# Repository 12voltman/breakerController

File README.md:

# breakerController
Chainable system for internet control of remotely switchable breakers

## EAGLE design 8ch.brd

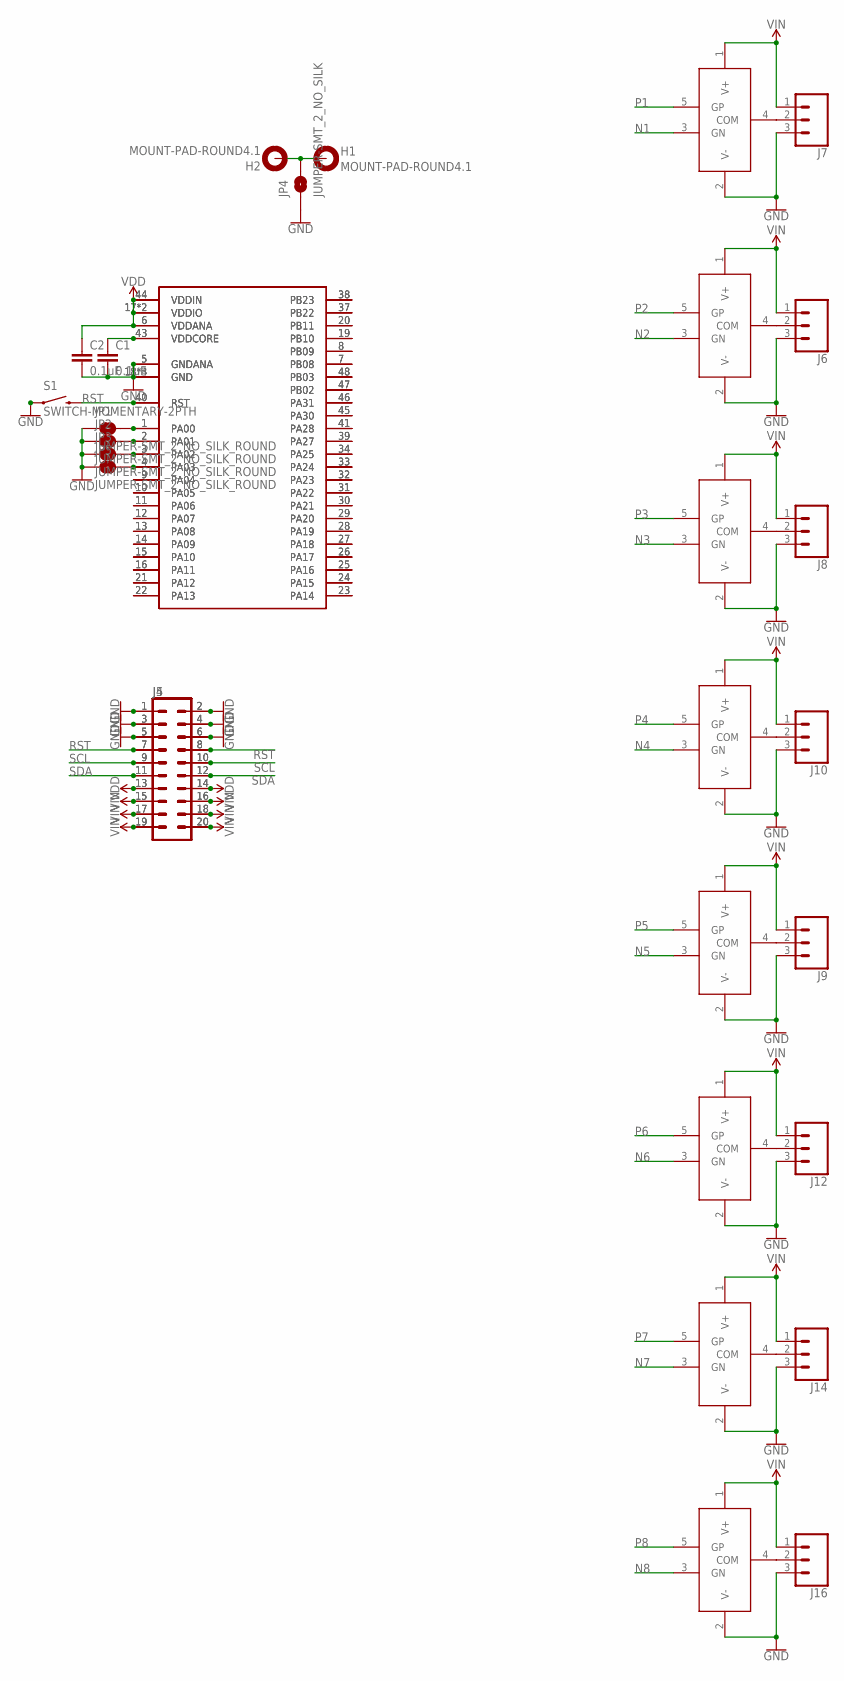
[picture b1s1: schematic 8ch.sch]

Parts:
C1, C2: 0.1uF; 0603
H1, H2: MOUNT-PAD-ROUND4.1; 4,1-PAD
J4, J5: CONN_10X2; 2X10
J6, J7, J8, J9, J10, J12, J14, J16: CONN_03-SCREW-5MM; SCREWTERMINAL-5MM-3
JP1, JP2, JP3, JP5: JUMPER-SMT_2_NO_SILK_ROUND; SMT-JUMPER_2_NO_SILK_ROUND
JP4: JUMPER-SMT_2_NO_SILK; SMT-JUMPER_2_NO_SILK
S1: SWITCH-MOMENTARY-2PTH; TACTILE-PTH
U$1: ATSAMD2G1A-M; QFN48_7X7
U$2, U$3, U$4, U$5, U$6, U$8, U$10, U$12: COMPBJT; SOT23-5
U$7: ATSAMD2G1A-A; TQFP48_7X7

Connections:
GND: C1.2, C2.2, J4.1, J4.2, J4.3, J4.4, J4.5, J4.6, J5.1, J5.2, J5.3, J5.4, J5.5, J5.6, J6.3, J7.3, J8.3, J9.3, J10.3, J12.3, J14.3, J16.3, JP1.1, JP2.1, JP3.1, JP4.1, JP5.1, S1.1, S1.2 (1), U$1.5 (GNDANA), U$1.18 (GND), U$1.35 (GND), U$1.42 (GND), U$1.EXP (GND), U$2.2 (V-), U$3.2 (V-), U$4.2 (V-), U$5.2 (V-), U$6.2 (V-), U$7.5 (GNDANA), U$7.18 (GND), U$7.35 (GND), U$7.42 (GND), U$8.2 (V-), U$10.2 (V-), U$12.2 (V-)
N1: U$3.3 (GN)
N2: U$2.3 (GN)
N3: U$4.3 (GN)
N4: U$6.3 (GN)
N5: U$5.3 (GN)
N6: U$8.3 (GN)
N7: U$10.3 (GN)
N8: U$12.3 (GN)
unnamed: H1.B4,1, H2.B4,1, JP4.2
unnamed: J6.2, U$2.4 (COM)
unnamed: J7.2, U$3.4 (COM)
unnamed: J8.2, U$4.4 (COM)
unnamed: J9.2, U$5.4 (COM)
unnamed: J10.2, U$6.4 (COM)
unnamed: C1.1, U$1.43 (VDDCORE), U$7.43 (VDDCORE)
unnamed: J12.2, U$8.4 (COM)
unnamed: J14.2, U$10.4 (COM)
unnamed: J16.2, U$12.4 (COM)
unnamed: JP1.2, U$1.1 (PA00), U$7.1 (PA00)
unnamed: JP2.2, U$1.2 (PA01), U$7.2 (PA01)
unnamed: JP3.2, U$1.3 (PA02), U$7.3 (PA02)
unnamed: JP5.2, U$1.4 (PA03), U$7.4 (PA03)
unnamed: U$1.9 (PA04), U$7.9 (PA04)
unnamed: U$1.10 (PA05), U$7.10 (PA05)
unnamed: U$1.11 (PA06), U$7.11 (PA06)
unnamed: U$1.12 (PA07), U$7.12 (PA07)
unnamed: U$1.13 (PA08), U$7.13 (PA08)
unnamed: U$1.14 (PA09), U$7.14 (PA09)
unnamed: U$1.15 (PA10), U$7.15 (PA10)
unnamed: U$1.16 (PA11), U$7.16 (PA11)
unnamed: U$1.21 (PA12), U$7.21 (PA12)
unnamed: U$1.22 (PA13), U$7.22 (PA13)
unnamed: U$1.23 (PA14), U$7.23 (PA14)
unnamed: U$1.24 (PA15), U$7.24 (PA15)
unnamed: U$1.25 (PA16), U$7.25 (PA16)
unnamed: U$1.26 (PA17), U$7.26 (PA17)
unnamed: U$1.27 (PA18), U$7.27 (PA18)
unnamed: U$1.28 (PA19), U$7.28 (PA19)
unnamed: U$1.29 (PA20), U$7.29 (PA20)
unnamed: U$1.30 (PA21), U$7.30 (PA21)
unnamed: U$1.31 (PA22), U$7.31 (PA22)
unnamed: U$1.32 (PA23), U$7.32 (PA23)
unnamed: U$1.33 (PA24), U$7.33 (PA24)
unnamed: U$1.34 (PA25), U$7.34 (PA25)
unnamed: U$1.41 (PA28), U$7.41 (PA28)
unnamed: U$1.45 (PA30), U$7.45 (PA30)
unnamed: U$1.46 (PA31), U$7.46 (PA31)
unnamed: U$1.47 (PB02), U$7.47 (PB02)
unnamed: U$1.48 (PB03), U$7.48 (PB03)
unnamed: U$1.7 (PB08), U$7.7 (PB08)
unnamed: U$1.8 (PB09), U$7.8 (PB09)
unnamed: U$1.19 (PB10), U$7.19 (PB10)
unnamed: U$1.20 (PB11), U$7.20 (PB11)
unnamed: U$1.37 (PB22), U$7.37 (PB22)
unnamed: U$1.38 (PB23), U$7.38 (PB23)
unnamed: U$1.39 (PA27), U$7.39 (PA27)
P1: U$3.5 (GP)
P2: U$2.5 (GP)
P3: U$4.5 (GP)
P4: U$6.5 (GP)
P5: U$5.5 (GP)
P6: U$8.5 (GP)
P7: U$10.5 (GP)
P8: U$12.5 (GP)
RST: J4.7, J4.8, J5.7, J5.8, S1.3 (2), S1.4 (2), U$1.40 (RST), U$7.40 (RST)
SCL: J4.9, J4.10, J5.9, J5.10
SDA: J4.11, J4.12, J5.11, J5.12
VDD: C2.1, J4.13, J4.14, J5.13, J5.14, U$1.6 (VDDANA), U$1.17 (VDDIO), U$1.36 (VDDIO), U$1.44 (VDDIN), U$7.6 (VDDANA), U$7.17 (VDDIO), U$7.36 (VDDIO), U$7.44 (VDDIN)
VIN: J4.15, J4.16, J4.17, J4.18, J4.19, J4.20, J5.15, J5.16, J5.17, J5.18, J5.19, J5.20, J6.1, J7.1, J8.1, J9.1, J10.1, J12.1, J14.1, J16.1, U$2.1 (V+), U$3.1 (V+), U$4.1 (V+), U$5.1 (V+), U$6.1 (V+), U$8.1 (V+), U$10.1 (V+), U$12.1 (V+)

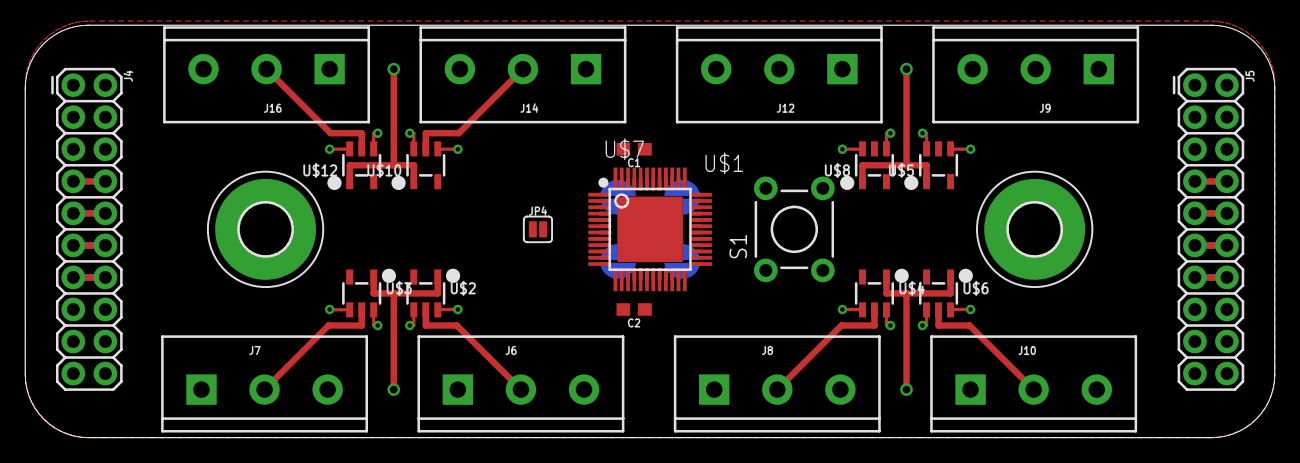
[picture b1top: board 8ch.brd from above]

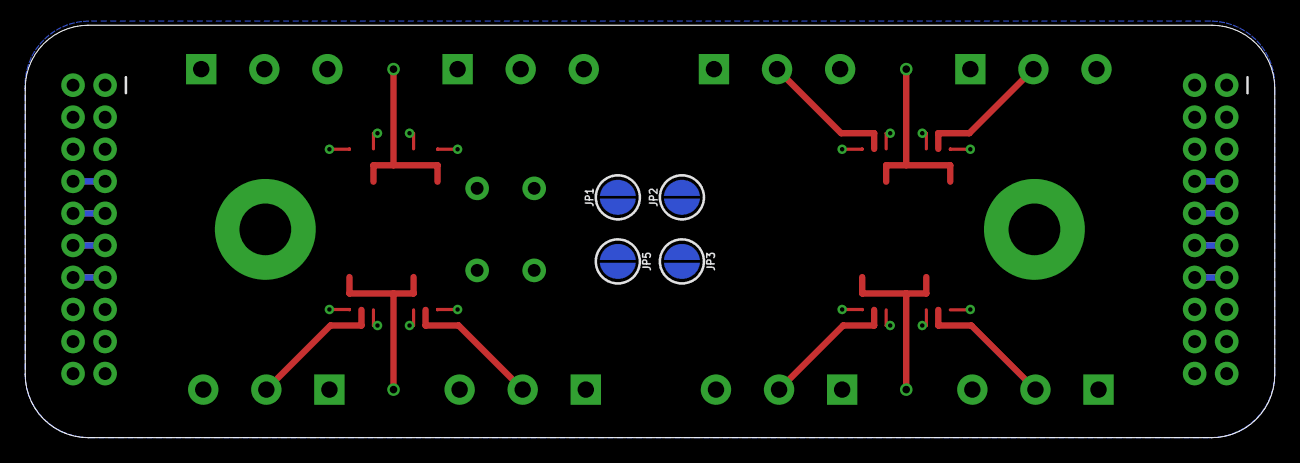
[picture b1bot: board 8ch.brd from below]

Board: 2 copper layers, 99.0 x 32.7 mm, 30 parts (4 on the bottom side), 54 nets.

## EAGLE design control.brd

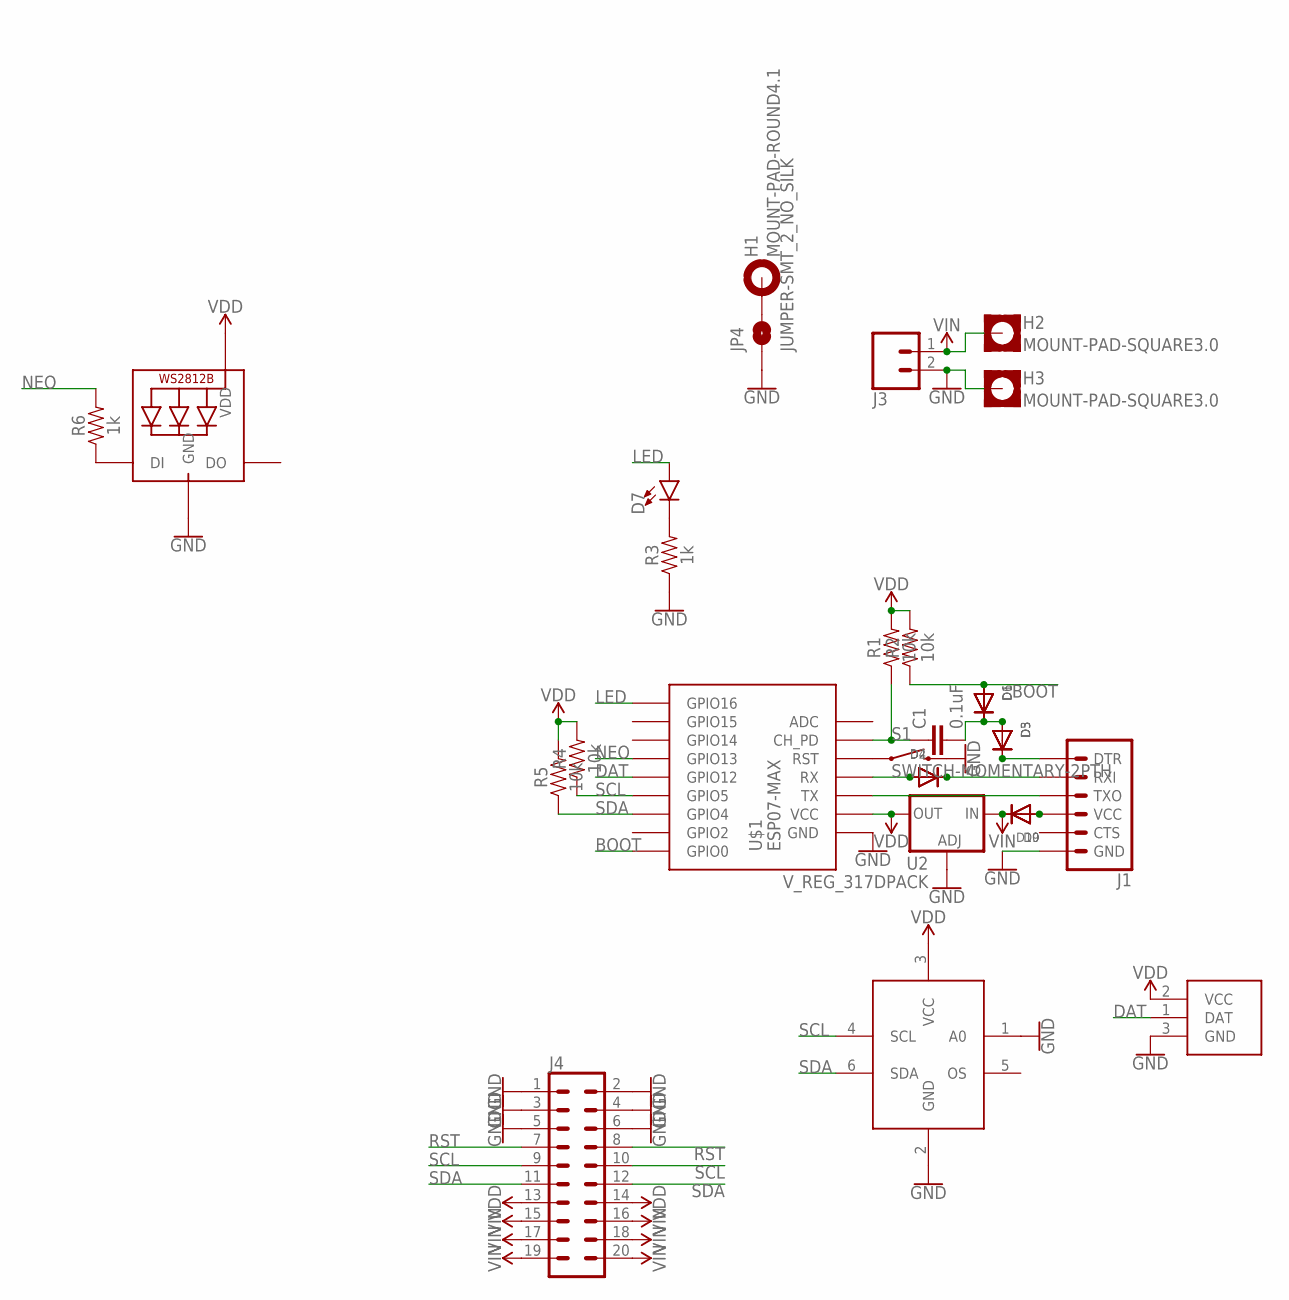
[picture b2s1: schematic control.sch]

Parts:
C1: 0.1uF; 0603
D1, D2, D3, D9: DIODESOD-123; SOD-123
D4, D5, D6, D10: DIODE_SOD-123FL; SOD-123FL
D7: LED0603; LED-0603
H1: MOUNT-PAD-ROUND4.1; 4,1-PAD
H2, H3: MOUNT-PAD-SQUARE3.0; 3,0-PAD-SQUARE
J1: 6_PIN_SERIAL_TARGETSILK; 6_PIN_SERIAL_TARGET_SIDE_W_SILK
J3: CONN_025MM; SCREWTERMINAL-5MM-2
J4: CONN_10X2; 2X10
JP4: JUMPER-SMT_2_NO_SILK; SMT-JUMPER_2_NO_SILK
LED1: WS2812BCOMBO; COMBONEO
R1, R2, R4, R5: 10k; 0603
R3, R6: 1k; 0603
S1: SWITCH-MOMENTARY-2PTH; TACTILE-PTH
U2: V_REG_317DPACK; V-REG_DPACK
U$1: ESP07-MAX
U$2: PCT2075GV; SOT23-6
U$3: ATSHA204A; SOT23

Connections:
BOOT: D1.A, D6.A, R2.1, U$1.P11 (GPIO0)
DAT: U$1.P05 (GPIO12), U$3.1 (DAT)
GND: H3.B3,0, J1.P$6 (GND), J3.2, J4.1, J4.2, J4.3, J4.4, J4.5, J4.6, JP4.1, LED1.VSS1 (GND), LED1.VSS2 (GND), R3.1, S1.3 (2), S1.4 (2), U2.1 (ADJ), U$1.P08 (GND), U$2.1 (A0), U$2.2 (GND), U$3.3 (GND)
LED: D7.A, U$1.P03 (GPIO16)
unnamed: H1.B4,1, JP4.2
unnamed: C1.1, R1.1, U$1.P02 (CH_PD)
unnamed: D2.A, D4.A, U$1.P14 (RX)
unnamed: J1.P$2 (TXO), U$1.P15 (TX)
unnamed: S1.1, S1.2 (1), U$1.P00 (RST)
unnamed: LED1.DIN1 (DI), LED1.DIN2 (DI), R6.1
unnamed: D2.C, D4.C, J1.P$3 (RXI)
unnamed: D3.C, D5.C, J1.P$1 (DTR)
unnamed: D7.C, R3.2
unnamed: D9.A, D10.A, J1.P$4 (VCC)
unnamed: C1.2, D1.C, D3.A, D5.A, D6.C
NEO: R6.2, U$1.P06 (GPIO13)
RST: J4.7, J4.8
SCL: J4.9, J4.10, R4.1, U$1.P12 (GPIO5), U$2.4 (SCL)
SDA: J4.11, J4.12, R5.1, U$1.P13 (GPIO4), U$2.6 (SDA)
VDD: J4.13, J4.14, LED1.VDD1 (VDD), LED1.VDD2 (VDD), R1.2, R2.2, R4.2, R5.2, U2.4 (OUT), U$1.P07 (VCC), U$2.3 (VCC), U$3.2 (VCC)
VIN: D9.C, D10.C, H2.B3,0, J3.1, J4.15, J4.16, J4.17, J4.18, J4.19, J4.20, U2.3 (IN)

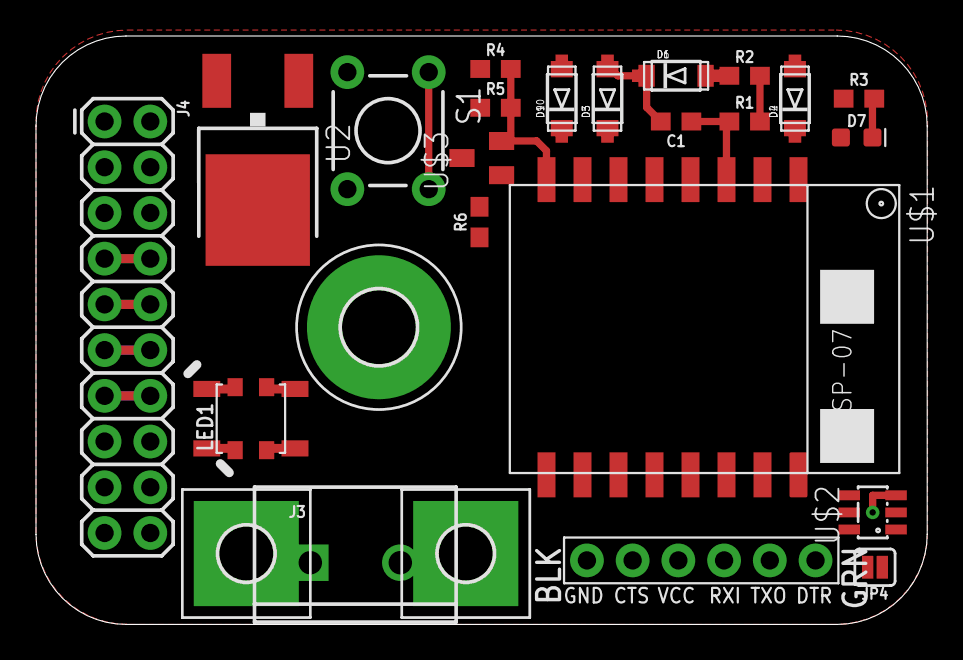
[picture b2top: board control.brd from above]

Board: 2 copper layers, 49.5 x 32.7 mm, 29 parts (0 on the bottom side), 21 nets.

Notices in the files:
parts and their libraries:
SparkFun-Connectors: Licensing: Creative Commons ShareAlike 4.0 International - https://creativecommons.org/licenses/by-sa/4.0
